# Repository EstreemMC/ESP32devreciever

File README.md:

# ESP32devreciever
An addon for my gamecube portable to enable wireless communications. The reciever will work for wireless gamecube controller(s) as well as wireless code upload for macros and inputs from a computer.

For the receiver, data integrity is vital for a solid wireless connection. I'd also like to be able to store macro files on the receiver, which should be activated by a hotkey or button combination. Connection should be seamless and integrated. Thankfully, no voltage regulators or power supplies are needed; however, to make flashing easier, I will incorporate a low level voltage regulator for the USB-C spec. On the portable itself, VIN will be supplied by the RVL-PMS-2, which has 3v3 out.

This should take little to no space. Minimizing outputs(only 17IO and 1 PWM in) should only require a maximum of 20 pins, 10 on each side of the motherboard(including 1 for 3.3v and 1 for ground. No debug to minimize space requirements. I need to satisfy the IO requirements for most of these pins. 

Utilizing the ESP32-WROOM-S3-N16 should be perfect; high flash memory, integrated SOC, and all the functionality of an ESP32. With that, I'll begin the schematic.

Finished developing the schematic, most components were brought over from the transmitter made earlier. Working from a new computer so I had to re download and modify footprint libraries. Smaller voltage regulator, limited my GPIO output pins severely so I could fit everything with just 20 jumper pins. PCB routing is going to be a pin, since I'll be using a 2layer board this time and need a much more compact PCB.

For some reason, this PCB layout and routing was infinitely more difficult than my last. I can attribute most of the difficulties to the dramatically smaller size and the lack of 4 layers, with me settling for just two. overall, I'm really happy with the way it turned out and I can't wait to implement it on my actual console!

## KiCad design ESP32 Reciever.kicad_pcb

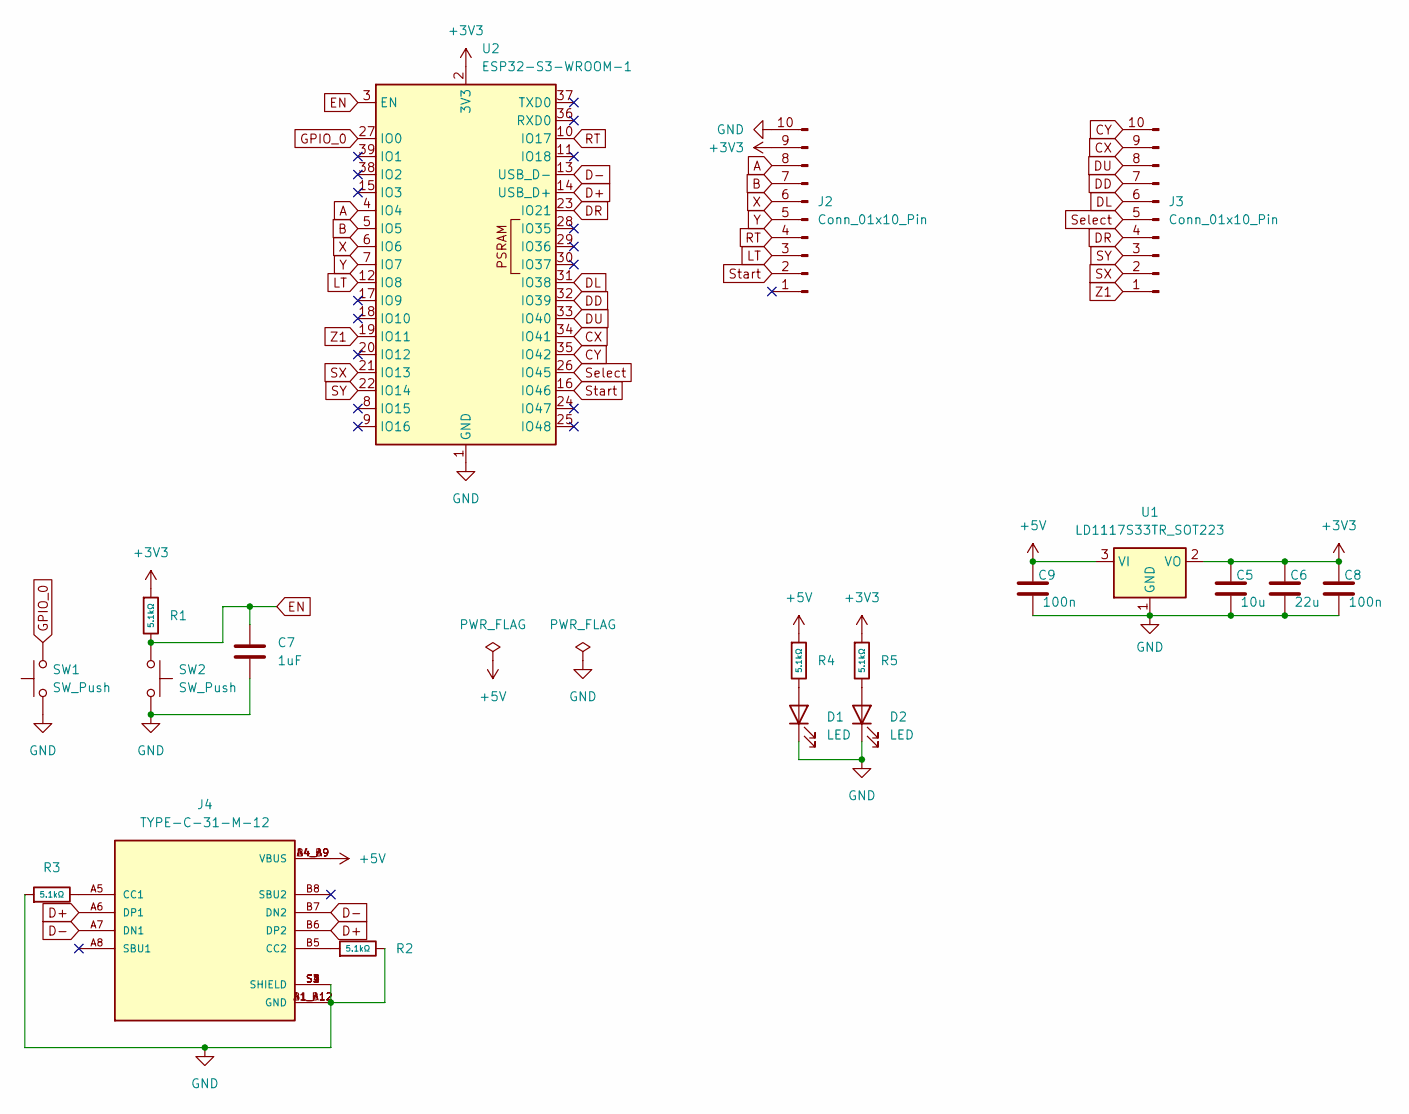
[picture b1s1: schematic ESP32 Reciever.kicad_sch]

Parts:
C5: 10u; C_0603_1608Metric
C6: 22u; C_0603_1608Metric
C7: 1uF; C_0603_1608Metric
C8, C9: 100n; C_0603_1608Metric
D1, D2: LED; LED_0603_1608Metric
J2, J3: Conn_01x10_Pin; PinHeader_1x10_P2.54mm_Vertical
J4: TYPE-C-31-M-12; HRO_TYPE-C-31-M-12; PARTREV 2020.12.08
R1, R2, R3, R4, R5: 5.1kΩ; C_0603_1608Metric; Overload Voltage (Max) 75V; Tolerance ±1%; Part 0603WAF5101T5E; LCSC C23186
SW1, SW2: SW_Push; SW_SPST_B3S-1100
U1: LD1117S33TR_SOT223; SOT-223-3_TabPin2
U2: ESP32-S3-WROOM-1

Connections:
+3V3: C5.1, C6.1, C8.1, J2.9, R1.1, R5.1, U1.2 (VO), U2.2 (3V3)
+5V: C9.1, J4.A4_B9 (VBUS), J4.B4_A9 (VBUS), R4.1, U1.3 (VI)
A: J2.8, U2.4 (IO4)
B: J2.7, U2.5 (IO5)
CX: J3.9, U2.34 (IO41)
CY: J3.10, U2.35 (IO42)
D+: J4.A6 (DP1), J4.B6 (DP2), U2.14 (USB_D+)
D-: J4.A7 (DN1), J4.B7 (DN2), U2.13 (USB_D-)
DD: J3.7, U2.32 (IO39)
DL: J3.6, U2.31 (IO38)
DR: J3.4, U2.23 (IO21)
DU: J3.8, U2.33 (IO40)
EN: C7.2, R1.2, SW2.1, U2.3 (EN)
GND: C5.2, C6.2, C7.1, C8.2, C9.2, D1.1 (K), D2.1 (K), J2.10, J4.A1_B12 (GND), J4.B1_A12 (GND), J4.S1 (SHIELD), J4.S2 (SHIELD), J4.S3 (SHIELD), J4.S4 (SHIELD), R2.2, R3.1, SW1.1, SW2.2, U1.1 (GND), U2.1 (GND), U2.40 (GND), U2.41 (GND)
GPIO_0: SW1.2, U2.27 (IO0)
LT: J2.3, U2.12 (IO8)
unnamed: D1.2 (A), R4.2
unnamed: D2.2 (A), R5.2
unnamed: J4.A5 (CC1), R3.2
unnamed: J4.B5 (CC2), R2.1
RT: J2.4, U2.10 (IO17)
SX: J3.2, U2.21 (IO13)
SY: J3.3, U2.22 (IO14)
Select: J3.5, U2.26 (IO45)
Start: J2.2, U2.16 (IO46)
X: J2.6, U2.6 (IO6)
Y: J2.5, U2.7 (IO7)
Z1: J3.1, U2.19 (IO11)

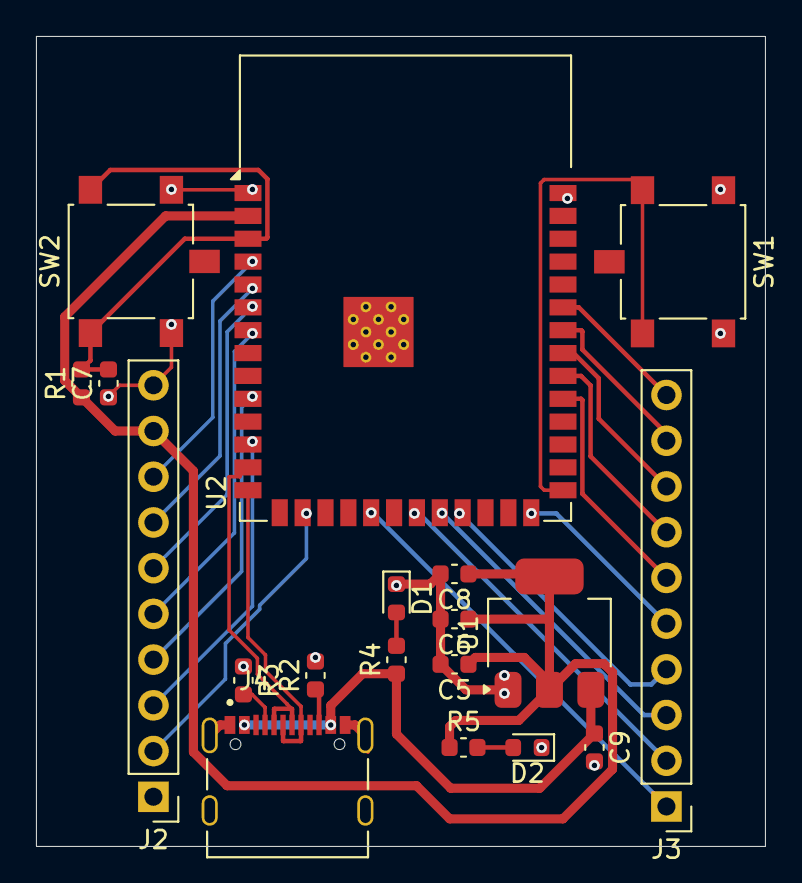
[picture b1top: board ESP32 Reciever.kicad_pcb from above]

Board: 4 copper layers, 40.5 x 45.0 mm, 19 parts (0 on the bottom side), 28 nets.

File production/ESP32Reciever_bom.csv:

Designator,Footprint,Quantity,Value,LCSC Part #
C5,0603,1,10u,
C6,0603,1,22u,
C7,0603,1,1uF,
"C8, C9",0603,2,100n,
"D1, D2",0603,2,LED,
"J2, J3",PinHeader_1x10_P2.54mm_Vertical,2,Conn_01x10_Pin,
J4,HRO_TYPE-C-31-M-12,1,TYPE-C-31-M-12,
"R1, R2, R3, R4, R5",0603,5,5.1kΩ,C23186
"SW1, SW2",SW_SPST_B3S-1100,2,SW_Push,
U1,SOT-223-3_TabPin2,1,LD1117S33TR_SOT223,
U2,ESP32-S3-WROOM-1,1,ESP32-S3-WROOM-1,

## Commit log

2025-11-29 Add files via upload
    Final PCB and schematic
